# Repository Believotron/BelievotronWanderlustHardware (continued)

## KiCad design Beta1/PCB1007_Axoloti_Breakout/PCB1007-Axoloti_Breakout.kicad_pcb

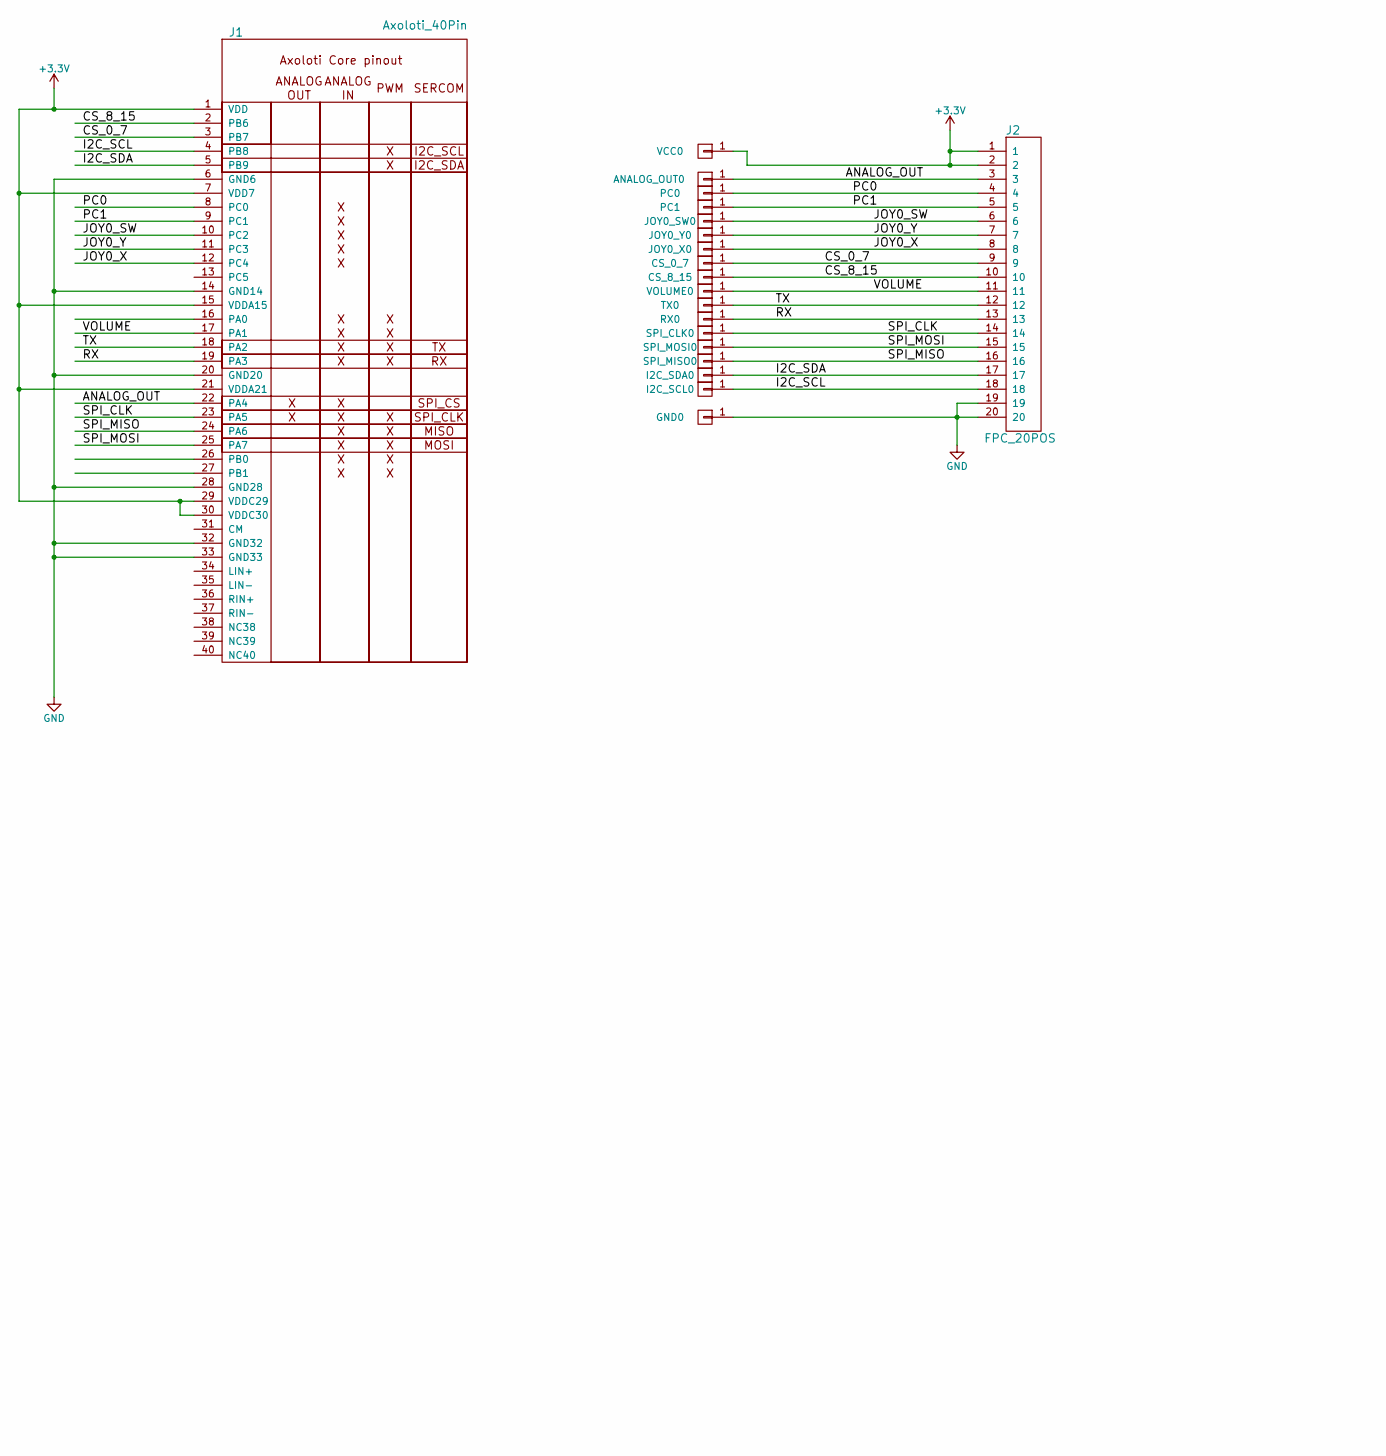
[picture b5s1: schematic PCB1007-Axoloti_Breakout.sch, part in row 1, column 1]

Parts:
ANALOG_OUT0: CONN_01X01; single_0.1; MPN ON_PCB
CS_0_7, CS_8_15: CONN_01X01; single_0.1; MPN ON_PCB
GND0: CONN_01X01; single_0.1; MPN ON_PCB
I2C_SCL0, I2C_SDA0: CONN_01X01; single_0.1; MPN ON_PCB
J1: Axoloti_40Pin; Axoloti-40x2_slim
J2: FPC_20POS; FFC_1MM_20POS_MOLEX_52271-2079
JOY0_SW0, JOY0_X0, JOY0_Y0: CONN_01X01; single_0.1; MPN ON_PCB
PC0, PC1: CONN_01X01; single_0.1; MPN ON_PCB
RX0: CONN_01X01; single_0.1; MPN ON_PCB
SPI_CLK0: CONN_01X01; single_0.1; MPN ON_PCB
SPI_MISO0: CONN_01X01; single_0.1; MPN ON_PCB
SPI_MOSI0: CONN_01X01; single_0.1; MPN ON_PCB
TX0: CONN_01X01; single_0.1; MPN ON_PCB
VCC0: CONN_01X01; single_0.1; MPN ON_PCB
VOLUME0: CONN_01X01; single_0.1; MPN ON_PCB

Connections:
+3V3: J1.1 (VDD), J1.7 (VDD7), J1.15 (VDDA15), J1.21 (VDDA21), J1.29 (VDDC29), J1.30 (VDDC30), J2.1, J2.2, VCC0.1
/ANALOG_OUT: ANALOG_OUT0.1, J1.22 (PA4), J2.3
/CS_0_7: CS_0_7.1, J1.3 (PB7), J2.9
/CS_8_15: CS_8_15.1, J1.2 (PB6), J2.10
/I2C_SCL: I2C_SCL0.1, J1.4 (PB8), J2.18
/I2C_SDA: I2C_SDA0.1, J1.5 (PB9), J2.17
/JOY0_SW: J1.10 (PC2), J2.6, JOY0_SW0.1
/JOY0_X: J1.12 (PC4), J2.8, JOY0_X0.1
/JOY0_Y: J1.11 (PC3), J2.7, JOY0_Y0.1
/PC0: J1.8 (PC0), J2.4, PC0.1
/PC1: J1.9 (PC1), J2.5, PC1.1
/RX: J1.19 (PA3), J2.13, RX0.1
/SPI_CLK: J1.23 (PA5), J2.14, SPI_CLK0.1
/SPI_MISO: J1.24 (PA6), J2.16, SPI_MISO0.1
/SPI_MOSI: J1.25 (PA7), J2.15, SPI_MOSI0.1
/TX: J1.18 (PA2), J2.12, TX0.1
/VOLUME: J1.17 (PA1), J2.11, VOLUME0.1
GND: GND0.1, J1.6 (GND6), J1.14 (GND14), J1.20 (GND20), J1.28 (GND28), J1.32 (GND32), J1.33 (GND33), J2.19, J2.20

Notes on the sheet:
2017-06-07
Believotron KnobCore 8CH Knob + Vol + 4CH Joy + 3CH OLED
Open source via MIT License github.com/Believotron/BelievotronWanderlustHardware
Date

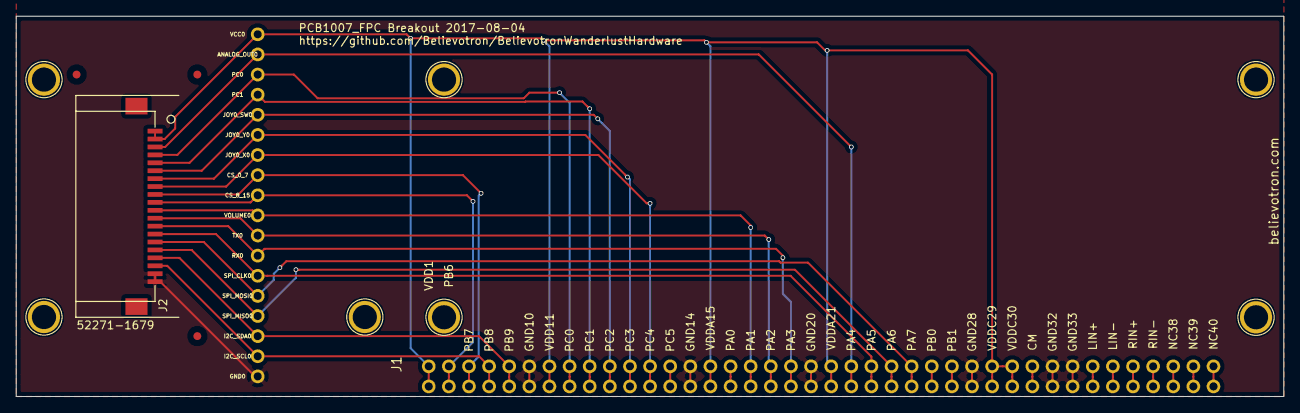
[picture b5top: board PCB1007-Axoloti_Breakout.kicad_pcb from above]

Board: 2 copper layers, 160.0 x 48.0 mm, 20 parts (0 on the bottom side), 18 nets.

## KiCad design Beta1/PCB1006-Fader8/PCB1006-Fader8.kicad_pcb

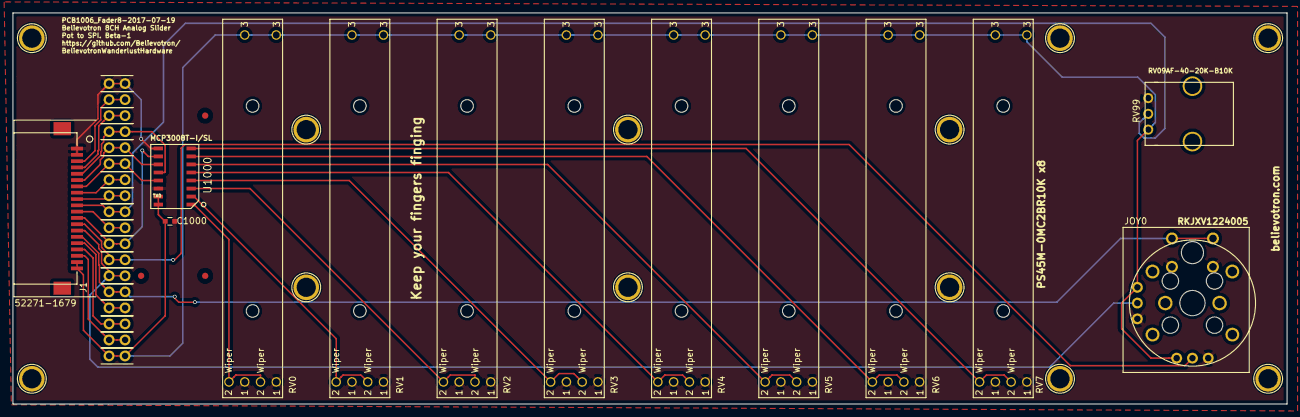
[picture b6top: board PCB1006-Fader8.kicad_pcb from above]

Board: 2 copper layers, 202.0 x 62.0 mm, 31 parts (0 on the bottom side), 26 nets.

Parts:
ANALOG_OUT0: CONN_01X01; TH_0.1_1x2_Jumper
C1000: 0.1u; C_0603
CS_0_7, CS_8_15: CONN_01X01; TH_0.1_1x2_Jumper
GND0: CONN_01X01; TH_0.1_1x2_Jumper
I2C_SCL0, I2C_SDA0: CONN_01X01; TH_0.1_1x2_Jumper
J1: FPC_20POS; FFC_1MM_20POS_MOLEX_52271-2079
JOY0: XYJOY_Alps; JOY_ALPS_RKJXV1224005
JOY0_SW0, JOY0_X0, JOY0_Y0: CONN_01X01; TH_0.1_1x2_Jumper
PC0, PC1: CONN_01X01; TH_0.1_1x2_Jumper
RV0, RV1, RV2, RV3, RV4, RV5, RV6, RV7: POT; LINEAR_POT_TT_ELECTRONICS_PS45M
RV99: POT; RV09AF-40-20K-B10K
RX0: CONN_01X01; TH_0.1_1x2_Jumper
SPI_CLK0: CONN_01X01; TH_0.1_1x2_Jumper
SPI_MISO0: CONN_01X01; TH_0.1_1x2_Jumper
SPI_MOSI0: CONN_01X01; TH_0.1_1x2_Jumper
TX0: CONN_01X01; TH_0.1_1x2_Jumper
U1000: MCP3008T-I/SL; SOIC-16
VCC0: CONN_01X01; TH_0.1_1x2_Jumper
VOLUME0: CONN_01X01; TH_0.1_1x2_Jumper

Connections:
+3V3: C1000.1, J1.19, J1.20, JOY0.J0-1, JOY0.J1-1, RV0.3, RV1.3, RV2.3, RV3.3, RV4.3, RV5.3, RV6.3, RV7.3, RV99.1, U1000.15, U1000.16, VCC0.1
/ANALOG_OUT: ANALOG_OUT0.1, J1.18
/CS_0_7: CS_0_7.1, J1.12, U1000.10
/CS_8_15: CS_8_15.1, J1.11
/I2C_SCL: I2C_SCL0.1, J1.3
/I2C_SDA: I2C_SDA0.1, J1.4
/JOY0_SW: J1.15, JOY0.SW1, JOY0_SW0.1
/JOY0_X: J1.13, JOY0.J0-2, JOY0_X0.1
/JOY0_Y: J1.14, JOY0.J1-2, JOY0_Y0.1
/P0: RV0.2, U1000.1
/P1: RV1.2, U1000.2
/P2: RV2.2, U1000.3
/P3: RV3.2, U1000.4
/P4: RV4.2, U1000.5
/P5: RV5.2, U1000.6
/P6: RV6.2, U1000.7
/P7: RV7.2, U1000.8
/PC0: J1.17, PC0.1
/PC1: J1.16, PC1.1
/RX: J1.8, RX0.1
/SPI_CLK: J1.7, SPI_CLK0.1, U1000.13
/SPI_MISO: J1.5, SPI_MISO0.1, U1000.12
/SPI_MOSI: J1.6, SPI_MOSI0.1, U1000.11
/TX: J1.9, TX0.1
/VOLUME: J1.10, RV99.2, VOLUME0.1
GND: C1000.2, GND0.1, J1.1, J1.2, JOY0.J0-3, JOY0.J1-3, JOY0.SW0, RV0.1, RV1.1, RV2.1, RV3.1, RV4.1, RV5.1, RV6.1, RV7.1, RV99.3, U1000.9, U1000.14

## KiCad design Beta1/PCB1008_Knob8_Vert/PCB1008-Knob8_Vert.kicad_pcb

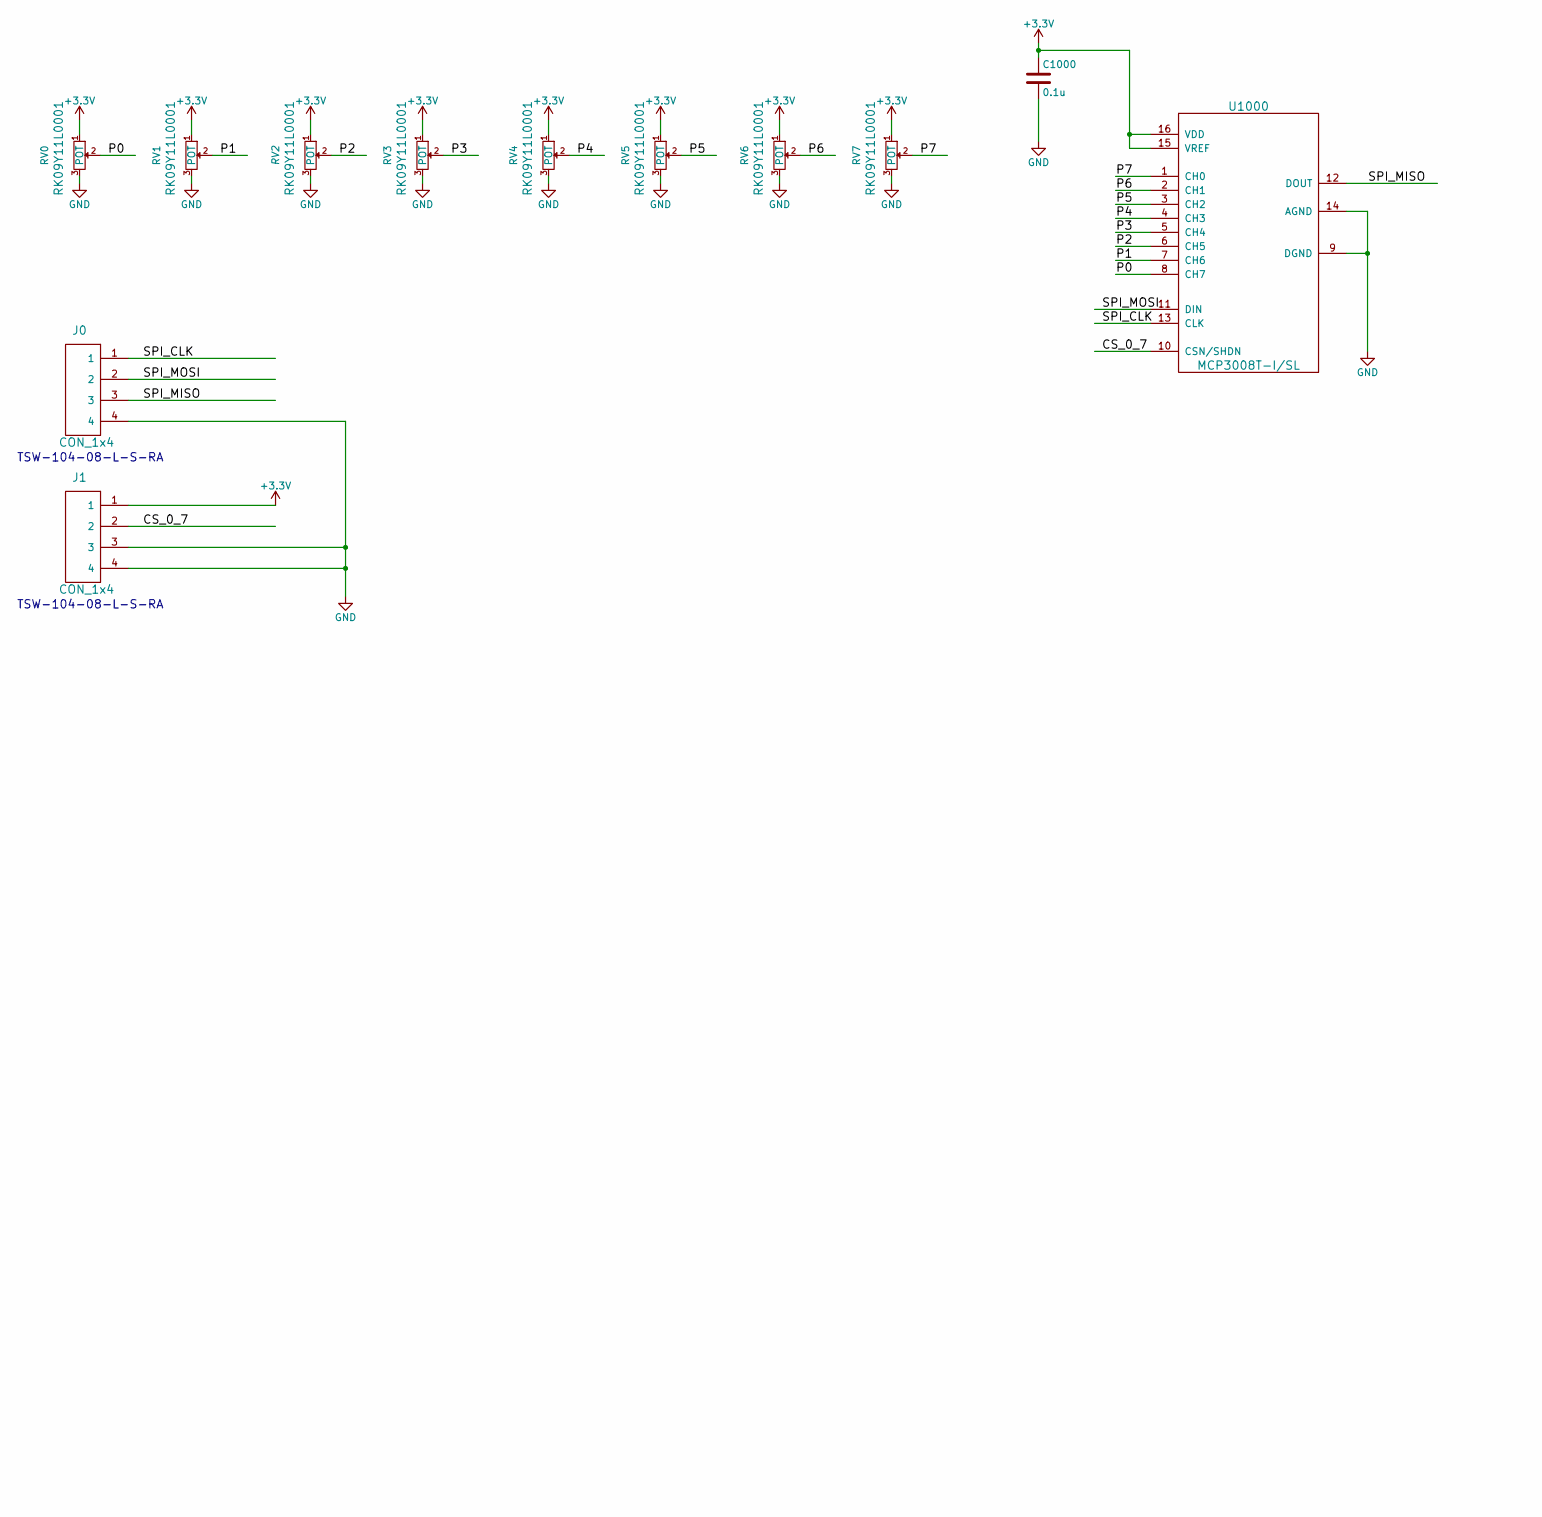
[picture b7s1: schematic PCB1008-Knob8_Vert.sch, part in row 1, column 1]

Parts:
C1000: 0.1u; C_0603; MPN CC0603KRX7R9BB104
J0, J1: CON_1x4; CON_0.1x4_SAMTEC_TSW-104-08-L-S-RA
RV0, RV1, RV2, RV3, RV4, RV5, RV6, RV7: POT; POT_ALPS_RK09Y11L0001; MPN RK09Y11L0001
U1000: MCP3008T-I/SL; SOIC-16; MPN MCP3008T-I/SL

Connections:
+3V3: C1000.1, J1.1, RV0.1, RV1.1, RV2.1, RV3.1, RV4.1, RV5.1, RV6.1, RV7.1, U1000.15 (VREF), U1000.16 (VDD)
/CS_0_7: J1.2, U1000.10 (CSN/SHDN)
/P0: RV0.2, U1000.8 (CH7)
/P1: RV1.2, U1000.7 (CH6)
/P2: RV2.2, U1000.6 (CH5)
/P3: RV3.2, U1000.5 (CH4)
/P4: RV4.2, U1000.4 (CH3)
/P5: RV5.2, U1000.3 (CH2)
/P6: RV6.2, U1000.2 (CH1)
/P7: RV7.2, U1000.1 (CH0)
/SPI_CLK: J0.1, U1000.13 (CLK)
/SPI_MISO: J0.3, U1000.12 (DOUT)
/SPI_MOSI: J0.2, U1000.11 (DIN)
GND: C1000.2, J0.4, J1.3, J1.4, RV0.3, RV1.3, RV2.3, RV3.3, RV4.3, RV5.3, RV6.3, RV7.3, U1000.9 (DGND), U1000.14 (AGND)

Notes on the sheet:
2017-06-07
Believotron KnobCore 8CH Knob + Vol + 4CH Joy + 3CH OLED
Open source via MIT License github.com/Believotron/BelievotronWanderlustHardware
Date
TSW-104-08-L-S-RA

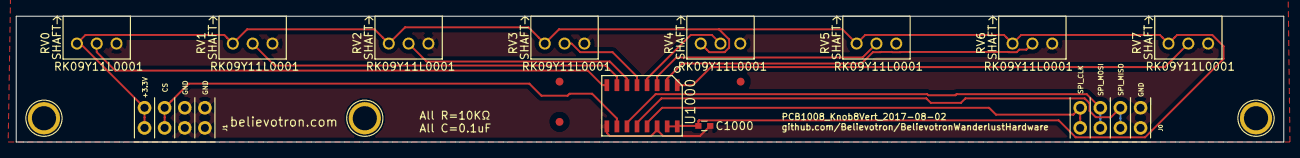
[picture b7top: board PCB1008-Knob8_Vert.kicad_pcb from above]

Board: 2 copper layers, 160.0 x 15.9 mm, 12 parts (0 on the bottom side), 14 nets.

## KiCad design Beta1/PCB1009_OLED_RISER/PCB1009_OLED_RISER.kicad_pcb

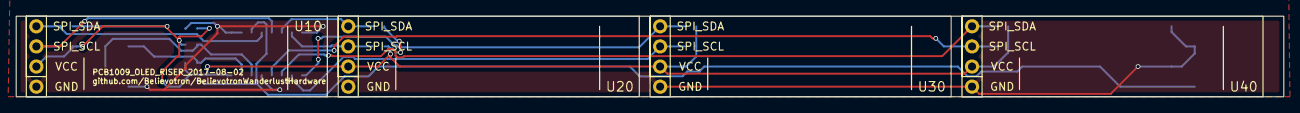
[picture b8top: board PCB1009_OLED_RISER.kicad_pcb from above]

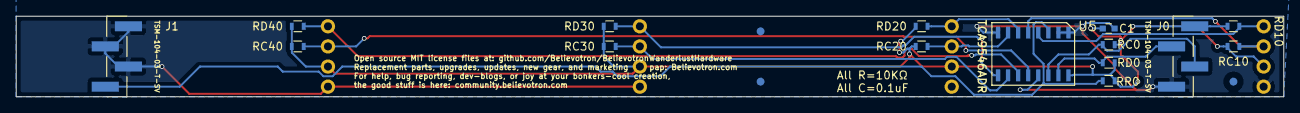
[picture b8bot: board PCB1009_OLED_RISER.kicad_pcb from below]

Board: 2 copper layers, 160.0 x 10.2 mm, 19 parts (15 on the bottom side), 13 nets.

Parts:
C1: 0.1u; C_0603
J0, J1: CON_1x4; HEADER_0.1x4_SMT_VERT_SAMTECTSM-104-03-T-SV
RC0, RC10, RC20, RC30, RC40: 10K; R_0603
RD0, RD10, RD20, RD30, RD40: 10K; R_0603
RR0: 10K; R_0603
U5: I2C_1x4MUX_TCA9546A; SOIC-16_1.27x5.4
U10, U20, U30, U40: OLED_128x32_I2C; OLED_128x32

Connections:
+3V3: C1.1, J0.1, RC0.1, RC10.1, RC20.1, RC30.1, RC40.1, RD0.1, RD10.1, RD20.1, RD30.1, RD40.1, RR0.1, U5.16, U10.2, U20.2, U30.2, U40.2
/!OLED_RESET: J1.1, RR0.2, U5.3
/I2C_SCL: J0.3, RC0.2, U5.14
/I2C_SCL0: RC10.2, U5.5, U10.3
/I2C_SCL1: RC20.2, U5.7, U20.3
/I2C_SCL2: RC30.2, U5.10, U30.3
/I2C_SCL3: RC40.2, U5.12, U40.3
/I2C_SDA: J0.2, RD0.2, U5.15
/I2C_SDA0: RD10.2, U5.4, U10.4
/I2C_SDA1: RD20.2, U5.6, U20.4
/I2C_SDA2: RD30.2, U5.9, U30.4
/I2C_SDA3: RD40.2, U5.11, U40.4
GND: C1.2, J0.4, J1.2, J1.3, J1.4, U5.1, U5.2, U5.8, U5.13, U10.1, U20.1, U30.1, U40.1

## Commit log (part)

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2016-11-14 Created SCH, PCB, and gerbers for SMD to TH adapter board
2016-11-16 Added LED Strip and moved around the system architecture.
2016-11-17 Knob / LED Module WIP
2016-11-17 Placed all LED components
2016-11-17 Placed all LED strip components. Only routing remains
2016-11-18 Routed LED PCB; everything but 1 unconnected (or openGL render problem)
2016-11-18 Trimmed outside edges from 7.5 to hole to 3mm to hole. Courage.
2016-11-18 Fixed a math error and adjusted height of led board + component heights
2016-11-18 Duplicated row. Placed components and drill holes. Ready to be routed.
2016-11-18 Housekeeping files. Renamed Knob with LED to Knobs. Board is ready for Gerbers.
2016-11-18 Duplicated LED Strip to Keys.
2016-11-18 Housekeeping. Changed Prototyping (vague) to 3D Prints
2016-11-18 Added Duplicate row 0.1" header for novice daisy chaining / monitoring
2016-11-18 Converted vias to plated through holes. Vias are / can be tented over.
2016-11-18 Changed second row daisy chain from vias to plated TH. You know. For kids.
2016-11-18 Added PCB# and Flavortext
2016-11-18 Added PCB #
2016-11-18 Basic layout of synth
2016-11-19 Added 1 octave keyboard footprint and into pcb.
2016-11-19 Add MPR
2016-11-21 Finished placement and routing of 1/2 Height Keypads. Ready to export.
2016-12-15 Catchup Commit. Non-atomic, Refactored LED, Keyboard, KeyPAD, and Knobs PCBs
    LED: Changed chips. Cleaned up silkscreen text. Added some support
    mounting holes. Shrank height of board to avoid stackup. KeyPAD is
    updated with new footprint. Keyboard and Knobs are unknown.
2016-12-21 Created new 1 screw width columns for horizontal eurorack.
2016-12-31 Minor Fuss. Apologies.
2016-12-31 Added more footprints and symbols.
2017-01-02 Added footprint to library.
2017-01-03 Created gerbers for fab.
2017-01-03 Cloned Knobs, removed pots, added 2 XY Joysticks.
2017-01-03 Added board date / info.
2017-01-03 Cloned 2CH Joy Mez and replaced a Joy with a knob (volume)
2017-01-03 Cloned 16 CH Knob and created an 8 ch Joy board
2017-01-19 Updated Drill jig for 1599KTS Enclosure
2017-01-19 Sourced from supplier
2017-01-19 Created 3D Model to enclose the Axoloti. Large print.
2017-01-19 Added volume knob + XY Joy to Knobs 16 CH Board.
2017-01-19 Added Website URL top Knobs PCB
2017-01-23 Failed Joystick toppers. Can't print hole that small.
2017-01-26 Created MFG Jigs / DWGs for PCB enclosure mounting
2017-01-26 Created MFG files for Enclosure PCB Mount
2017-01-26 Created zcode
2017-01-26 Fixed unconnected net.
2017-01-26 Cleaned up old gerber files
2017-01-26 Moved mounting hole in by 2.54 mm to see if it would work.
2017-01-26 Removed design. Too complicated for fab.
2017-01-26 Moved to sub-dir
2017-01-26 Moved old designs to archive
2017-01-26 Moved project and renamed files to MPR121_TH_Adapter
2017-01-26 Moved. Renamed. Added "PCB1000-KNOBS" to PCB silk
2017-01-26 Moved. Renamed to PCB1002_LED32
2017-01-26 Renamed to Knobs16. Updated PCB Silk
2017-01-26 Reduced width by 5.08, equally L/R
2017-01-26 Added fiducial
2017-01-26 Renamed to PCB1001
2017-01-26 Renamed to Schematic to differentiate
2017-01-26 Renamed to PCB1002_Piano_16PAD
2017-01-27 Fixed dupe annotations
2017-01-27 Placement Done.
2017-01-27 Done routing.
2017-01-27 Added surplus padcap signal access to mezzanine
2017-01-27 Generated schematic
2017-02-02 Added CPT112S to PCB1002 fork -> PCB1003
    Components placed.
2017-02-03 Finished routing. Ready for proto.
2017-02-03 Filled in empty gnd hatch.
2017-02-03 Filled in more gnd hatch.
2017-02-11 Prototyping Enclosure. WIP.
2017-03-01 New enclosure designs
2017-03-01 Added project files to make the root file accessible.
2017-03-01 Pin swap reroute WIP.
2017-03-01 Ready for fab.
2017-03-02 Mid reroute. Move interference. Clean silk.
2017-03-02 Added labels on bottom. Added CS short to GND.
2017-03-02 Moved input connector to avoid interference w screw
2017-03-04 Files ready for fab.
2017-03-31 Updates to WIP enclosure design
2017-03-31 Increased width by 2U. Ready for FAB
2017-03-31 Generated 36U 3D models. Outdated in lieu of 38U.
2017-03-31 Outdated 36U files.
2017-03-31 Updated PCB Flavortext
2017-03-31 Changed from 36U to 38U. Ready for Fab.
2017-03-31 Remove old 3d files. was 36U.
2017-03-31 Wrong place
2017-03-31 Renamed to +MPR121, moved to archive
2017-03-31 Renamed folder +=CPT112S
2017-03-31 Renamed. Widened from 36U to 38U. Ready for Fab.
2017-03-31 Updated drivel, save after committ. Ready for fab.
2017-04-01 Added 40x3 Axoloti connector with screws.
2017-04-01 First pass schematic on translator board.
2017-04-01 Fixed small bugs, cleaned up the graphics
2017-04-01 Rough placement complete
2017-04-06 Cleaned up file locations
2017-05-16 Enclosure WIP
2017-05-16 Copied from PCB1000-Knobs16
2017-05-17 Created slimline version
2017-05-18 Added parts for OLED
2017-05-18 Added OLED to SCH. PCB needs update.
2017-05-18 PCB Placed, ready to route.
2017-05-19 Ready for fab
2017-05-30 Updated MPN to TCA9546ADR
2017-05-31 Initial Placement
2017-05-31 Added CYA TH for I2C3. Cleaned up Silkscreen.
2017-05-31 Added extra mounting hole
2017-06-01 First pass layout
2017-06-09 Cloned PCB1000 as boilerplate
2017-06-09 Added linear pot. What fun!
2017-06-09 Saved files sent to fab.
2017-06-09 Routing complete
2017-06-26 Added notches to Case
2017-06-26 Renamed from Fader16 to Fader8
2017-06-26 Core enclosure V1
2017-06-27 Created passable enclosure
2017-06-27 Added 10mm opposite User IO connectors for installation
2017-06-27 Moved/resized top plate holes
2017-06-28 Increased width of all vertical pieces for EZ install
2017-06-28 Changed OLED cutouts to fit proto
2017-06-28 Widened OLED cutout
2017-06-30 Fixed 3mm Shift
2017-06-30 Added extra OLED. WIP
2017-07-01 Added USB-K to SCH and rough placement
2017-07-03 Removed USB-K con, no room.
    Removed USB-K from PCB1005
    It's possible to fit it, but it would be a cluttered, bouncy mess.
2017-07-06 Updated silkscreen and pin position
2017-07-06 Added third row
2017-07-07 Cleaned up for printing
2017-07-07 Routed critical traces
2017-07-08 Deleted source, and reforked from PCB1005
2017-07-08 Removed duplicate pads
2017-07-08 SCH+Route complete
2017-07-11 PCB1006 ready for fab
2017-07-13 Expanded and rounded top and bottoms
2017-07-13 Created Joystick footprint from datasheet
    http://www.alps.com/prod/info/E/HTML/MultiControl/Potentiometer/RKJXK/RKJXV1224005.html#Photo
2017-07-13 Added circle to silkscreen to help lasercutting
2017-07-13 Added circle to help with lasercutting
2017-07-13 Deleted duplicatd pads
2017-07-13 High speed signals routed
2017-07-13 Initial routing complete. Waiting on pinouts to finish
2017-07-17 Changed Pin names to match device
2017-07-17 Moved Joystics to 30mm from Knobs
2017-07-17 Changed joystick to alps, moved, routed.
2017-07-17 housekeeping
2017-07-18 Saved plot settings
2017-07-19 Added FFC connectors
2017-07-19 Conversion to FFC WIP
2017-07-19 autosave
2017-07-19 Added 20 pos FFC
2017-07-19 Swapped USBK for FFC connector. Routed.
2017-07-28 Added 3D Files
2017-07-28 Proto WIP
2017-07-28 Forked PCB1005 to PCB1008
2017-07-28 Added potentiometer
2017-07-28 Added PN
2017-07-28 Converted old sch
    Added QTY 2, 1x4 connectors
    Changed Pots to 1M long life pot
    Removed OLED ckt
    Removed Joy ckt
2017-07-28 Added 0.1" 1x4 RA connector
2017-07-28 Added sym 1x4
2017-07-29 Finished rough placement and 3D model
2017-07-29 Created 3d step files
2017-07-29 Forked PCB1005 to PCB1009
2017-07-29 Added connector
2017-07-29 Reverted to correct path
2017-07-29 Rough placement WIP
2017-08-01 Creating 3D models
2017-08-01 Dead end. Kept for posterity
2017-08-02 Added a circle to show position of Centerpot
2017-08-02 Routed
2017-08-02 Finished routing
2017-08-02 Added !OLED_RESET
2017-08-03 WIP, building laser enclosure
2017-08-04 Updated connector pinouts. Ready for Fab
2017-08-04 Final save, Ready for Fab.
2017-08-04 Changed con pinout. Ready for Fab.
2017-08-04 Added FFC connector. Ready for fab
2017-08-15 save
2017-08-15 Not sure
2017-08-15 Respawned
2017-08-15 Readded pots and OLED. Placement done
2017-08-15 mid route
2017-08-15 Forked PCB1005 over PCB1008
2017-08-15 Renamed connectors. Already in netlist/pcb
2017-08-15 Removed Joysticks / OLED. Read for fab
2017-08-18 Good fit with current PCB.
2017-09-08 Updated Laser files for pilot build
2017-11-26 Enclosure updates
2017-11-28 Created variation laser cut file for Believotron Core enclosure
    Features 4x2 0.25" diameter holes with a pitch of 0.4" on top plate of Believotron Core standard enclosure.
2017-12-13 Created Beta 1 Enclosure files
2018-03-08 Added TH connector, updated board outline
2018-03-08 Created keytar laser cut files. Awaiting First Article Inspection
2018-03-08 Add FFC TH Connector
2018-03-08 Move debug vias to inside instead of outside to reduce footprint
2018-03-16 Corrected serial UART RX/TX nets
2018-03-17 Routed all traces on PCB1010, except VCC and GND
2018-03-17 Fully routed. WIP. Waiting on DFM review.
2018-03-19 Added Gerbers. Ready for fab.
2018-03-19 Sticky save. Now ready for fab.
2018-04-16 Created work instructions to make PCB1010_2018-03-16 work
    Cut Y signals, added jumpers
2018-04-16 Updated FFC footprint, flipped rows after prototype changeorder.
2018-04-16 Updated FFC footprint, Removed proto resistors, deleted all traces
2018-04-16 Removed signals from STM32 that weren't being changed.
    Removed SPI and control signals
    Removed PC0, PC1
    Signals now go directly from axoloti to PCB1005
2018-04-16 Mid-route
2018-04-18 Finished routing. Files ready for fab.
2018-04-18 Sticky save. Routing finished. Ready for fab.
2018-04-18 Created PCB1011 Protoboard. Files ready for fab.
2018-04-21 Basic Eurorack workshopping
2018-04-21 Fixed axo mounting holes
2018-05-21 WIP Eurorack enclosure dev
2018-05-21 Merged all four OLEDs for more stability
2018-05-21 Created documentation for assembly per user request. Info is presented in the community forum.
2018-05-21 WIP, porting 3D prints to Prusa printer
2018-06-05 Updated OLED jig
2018-06-05 Lasercut Eurorack WIP
2018-06-05 Added graphics to help installation
2018-06-27 Forked Joystick from PCB1005
2018-06-27 Development WIP
2018-06-27 WIP Eurorack 3D Print development
2018-07-16 WIP Keytar enclosure
2018-08-04 Forked PCB1005 and renamed to PCB1013 in advance of new design
2018-08-04 Rough placement
2018-08-04 Removed 40 pin header
2018-11-13 Housekeeping, moved files
2018-11-13 Files ready for fab. Prototyping new hole spacing for Wanderlust Faceplate.
2018-11-14 Housecleaning
2018-11-14 Sketching WIP
2018-11-14 Housekeeping; Moved to more intuitive location.
2018-11-15 Added more Eurorack sketches
2018-12-06 Organized into sub-folders and archived stale files.
2018-12-06 Generated prusa 3D print files
2018-12-06 Updated files for KiCad 5
2018-12-06 Created rudimentary Axoloti Core Dimensional drawing as a communication asset
2018-12-06 Created Eneric Eurorack Analog I/O Block Diagram Sketch
2018-12-28 Sketched new possible wanderlust architecture
2018-12-29 Trying out various configurations for the Wanderlust with a 2.4" color touchscreen.
2018-12-30 Moved something between layers.
2018-12-31 Continuing sketching on unified common circuit boards
2018-12-31 Further cohesion added to hardware line sketch
2018-12-31 Added power circuit board to eurorack modules. Highlighted ffc connector on different flavors of synths as different.
2019-01-01 Removed redundant eurorack workshop artboard/page
2019-01-01 Changed FFC connector to match LCD TFT display
2019-01-01 Added FFC con for 2.4" TFT Touch connector
2019-01-09 Added remaining pieces needed for an even set of six
2019-01-09 Added image and dimensional drawing to see if the screen can be integrated
2019-01-10 Added bottom / rear / front panels for material sourcing
2019-01-13 Added desktop first draft
2019-01-13 Moved joystick / knobs further up
2019-01-13 First draft of keytar with strap
2019-01-13 Removed Rejected Ideas
2019-01-13 Sketched out some solutions using Pi as navigator
2019-01-13 Consolidating features / effort
2019-01-13 Further simplified solution family
2019-02-01 WIP concept sketching
